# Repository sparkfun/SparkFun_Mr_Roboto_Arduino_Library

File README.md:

Mr. Roboto Kit
========================

[  
*Mr. Roboto Kit (KIT-11257)*](https://www.sparkfun.com/products/11257)

Mr. Roboto is an Arduino-compatible development board designed to be used as a teaching tool for Arduino programming. All of the surface mount components come pre-soldered so a few minutes of simple through-hole soldering is all it takes to get him up and running. After the kit is put together, the on board sensors, buzzer and LCD screen make an excellent platform for learning how to write code for physical computing.

Repository Contents
-------------------

* **/firmware** - Arduino example code
* **/hardware** - PCB design files (created with Eagle 6.1.0)

Product Versions
----------------

**[KIT-11257](https://www.sparkfun.com/products/11257) - Mr. Roboto Kit OEM packaging**  
The Mr. Roboto Kit in standard OEM packaging.

**[RTL-11384](https://www.sparkfun.com/products/11384) - Mr. Roboto Kit retail packaging**  
The Mr. Roboto Kit in a retail-ready plastic clam shell.

License Information
-------------------

All contents of this repository are released under [Creative Commons Share-alike 3.0](http://creativecommons.org/licenses/by-sa/3.0/).

Author
------

Jim Lindblom, [SparkFun Electronics](https://www.sparkfun.com)

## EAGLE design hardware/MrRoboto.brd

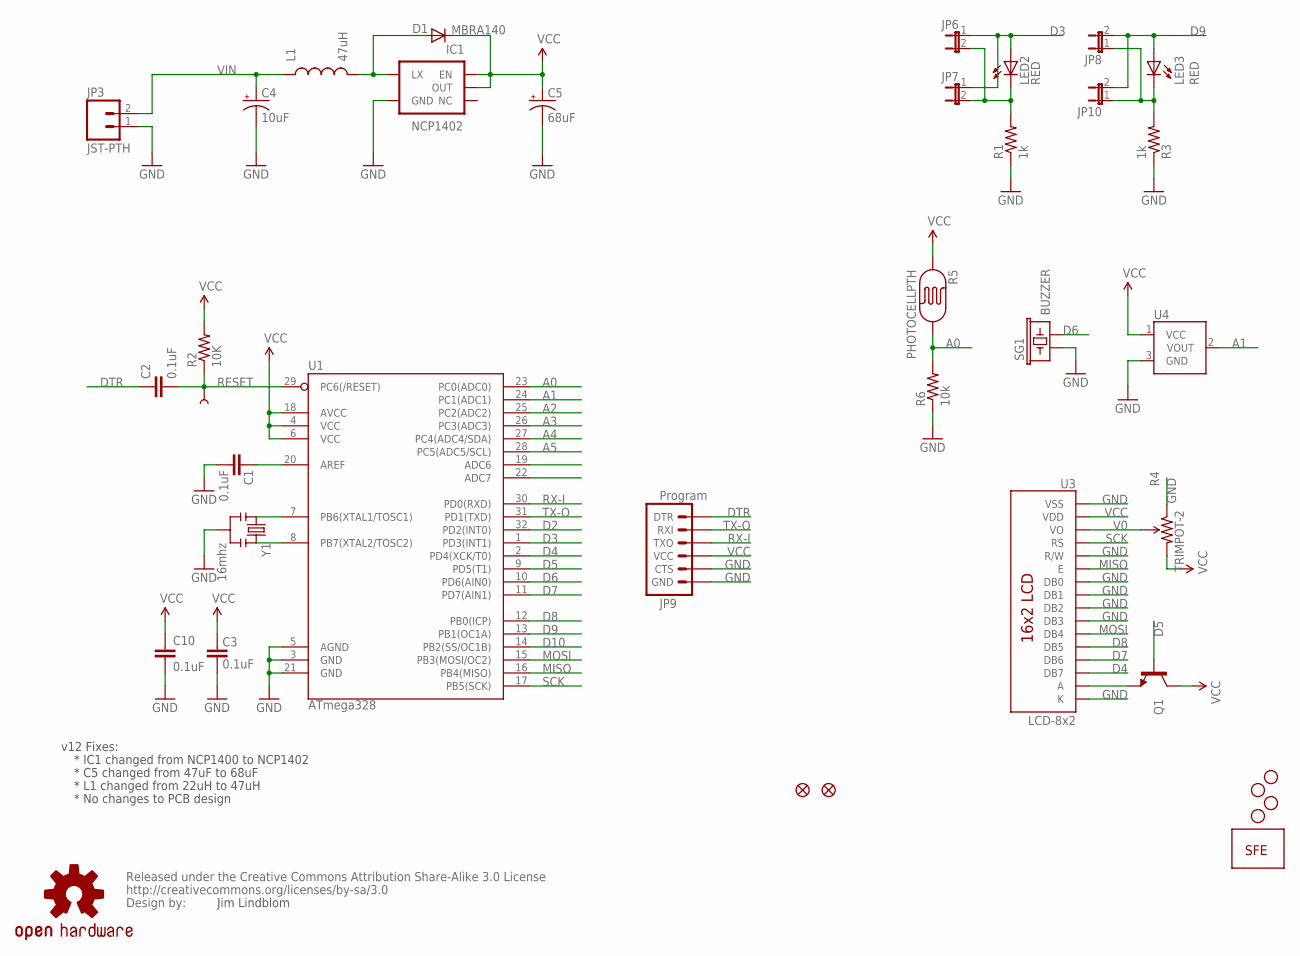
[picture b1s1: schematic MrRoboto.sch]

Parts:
C1, C2, C3, C10: 0.1uF; 0402-CAP
C4: 10uF; EIA3216
C5: 68uF; EIA3528
D1: MBRA140; SMA-DIODE
IC1: NCP1402; SOT23-5
JP1, JP2, JP4, JP5: Long, Plastic; STAND-OFF
JP3: JST-PTH; JST-2-PTH-KIT
JP6, JP7, JP8, JP10: JUMPER-2SMD-NO-NS; SJ_2S-NO-NS
JP9: Program; 1X06-KIT
JP11, JP12: FIDUCIAL1X2.5; FIDUCIAL-1X2.5
L1: 47uH; CR54
LED2, LED3: RED; LED5MM-KIT
Q1: TRANSISTOR_NPNSOT23; SOT23
R1, R3: 1k; AXIAL-0.3-KIT
R2: 10K; 0402-RES
R4: TRIMPOT-2; TRIMPOT_TC33
R5: PHOTOCELLPTH; PHOTOCELL-KIT
R6: 10k; 0402-RES
SG1: BUZZER; BUZZER-12MM-NS-KIT
TP1: TP; PAD.03X.05
U1: ATmega328; TQFP32-08
U3: LCD-8x2; LCD-8X2-KIT
U4: TMP36TO-92-KIT; TO-92-KIT
U$1: CREATIVE_COMMONS
U$2: OSHW-LOGOM; OSHW-LOGO-M
U$3: LOGO-SFENEW; SFE-NEW-WEBLOGO
Y1: 16mhz; RESONATOR-SMD

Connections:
A0: R5.2, R6.2, U1.23 (PC0(ADC0))
A1: U1.24 (PC1(ADC1)), U4.2 (VOUT)
A2: U1.25 (PC2(ADC2))
A3: U1.26 (PC3(ADC3))
A4: U1.27 (PC4(ADC4/SDA))
A5: U1.28 (PC5(ADC5/SCL))
AREF: C1.2, U1.20 (AREF)
D2: U1.32 (PD2(INT0))
D3: JP6.1, JP7.1, LED2.A, U1.1 (PD3(INT1))
D4: U1.2 (PD4(XCK/T0)), U3.14 (DB7)
D5: Q1.1 (B), U1.9 (PD5(T1))
D6: SG1.- (2), U1.10 (PD6(AIN0))
D7: U1.11 (PD7(AIN1)), U3.13 (DB6)
D8: U1.12 (PB0(ICP)), U3.12 (DB5)
D9: JP8.2, JP10.2, LED3.A, U1.13 (PB1(OC1A))
D10: U1.14 (PB2(SS/OC1B))
DTR: C2.1, JP9.1 (DTR)
GND: C1.1, C3.1, C4.C (-), C5.C (-), C10.2, IC1.4 (GND), JP3.1, JP9.5 (CTS), JP9.6 (GND), R1.P$1 (1), R3.P$1 (1), R4.1 (CCW), R6.1, SG1.+ (1), U1.3 (GND), U1.5 (AGND), U1.21 (GND), U3.1 (VSS), U3.5 (R/W), U3.7 (DB0), U3.8 (DB1), U3.9 (DB2), U3.10 (DB3), U3.16 (K), U4.3 (GND), Y1.2
MISO: U1.16 (PB4(MISO)), U3.6 (E)
MOSI: U1.15 (PB3(MOSI/OC2)), U3.11 (DB4)
unnamed: D1.A, IC1.5 (LX), L1.P$2 (2)
unnamed: Q1.2 (E), U3.15 (A)
unnamed: U1.7 (PB6(XTAL1/TOSC1)), Y1.1
unnamed: JP8.1, JP10.1, LED3.K (C), R3.P$2 (2)
unnamed: U1.8 (PB7(XTAL2/TOSC2)), Y1.3
unnamed: JP6.2, JP7.2, LED2.K (C), R1.P$2 (2)
RESET: C2.2, R2.1, TP1.P$1, U1.29 (PC6(/RESET))
RX-I: JP9.3 (TXO), U1.30 (PD0(RXD))
SCK: U1.17 (PB5(SCK)), U3.4 (RS)
TX-O: JP9.2 (RXI), U1.31 (PD1(TXD))
V0: R4.2 (WIPER), U3.3 (VO)
VCC: C3.2, C5.A (+), C10.1, D1.C, IC1.1 (EN), IC1.2 (OUT), JP9.4 (VCC), Q1.3 (C), R2.2, R4.3 (CW), R5.1, U1.4 (VCC), U1.6 (VCC), U1.18 (AVCC), U3.2 (VDD), U4.1 (VCC)
VIN: C4.A (+), JP3.2, L1.P$1 (1)

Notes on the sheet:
Jim Lindblom
v12 Fixes:
* IC1 changed from NCP1400 to NCP1402
* C5 changed from 47uF to 68uF
* L1 changed from 22uH to 47uH
* No changes to PCB design

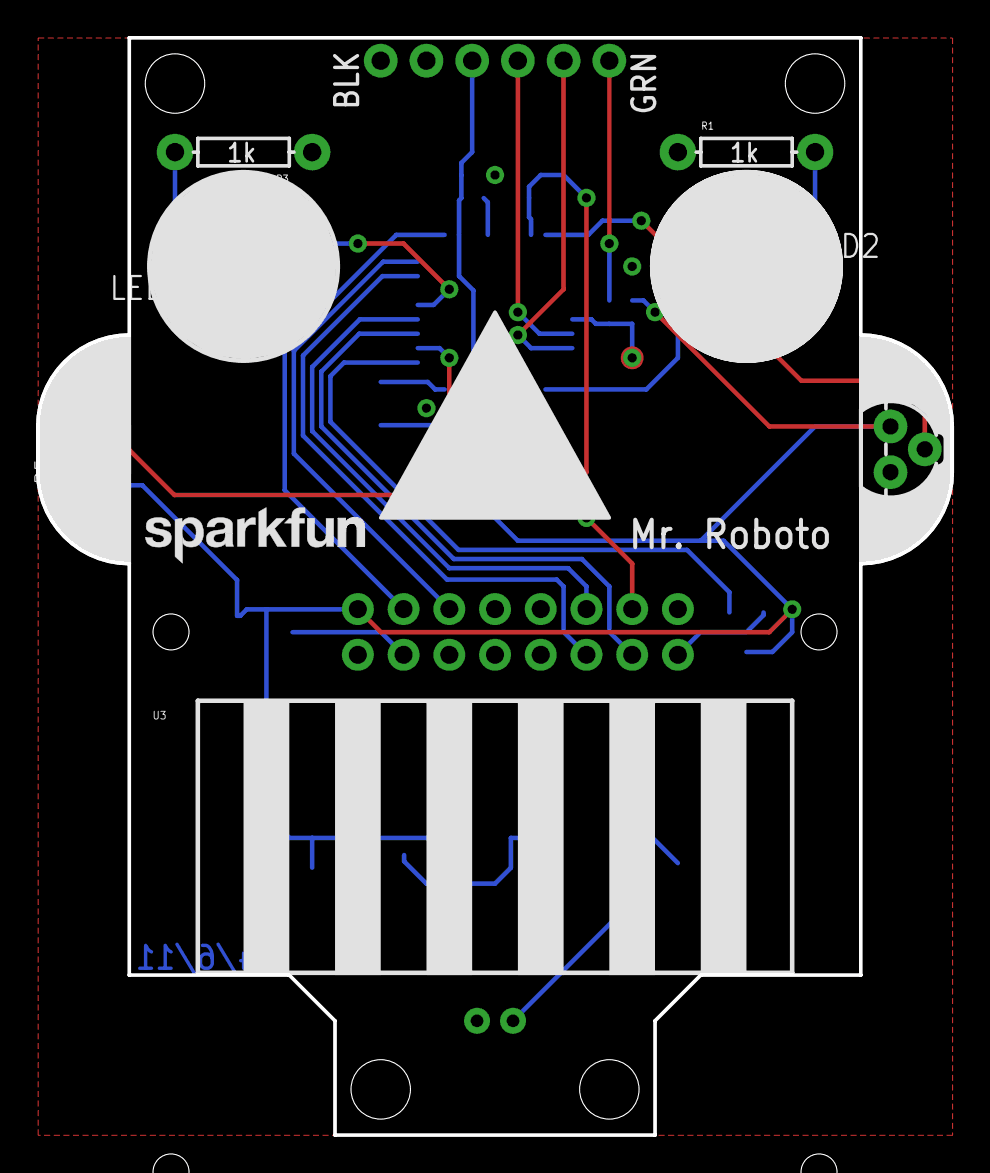
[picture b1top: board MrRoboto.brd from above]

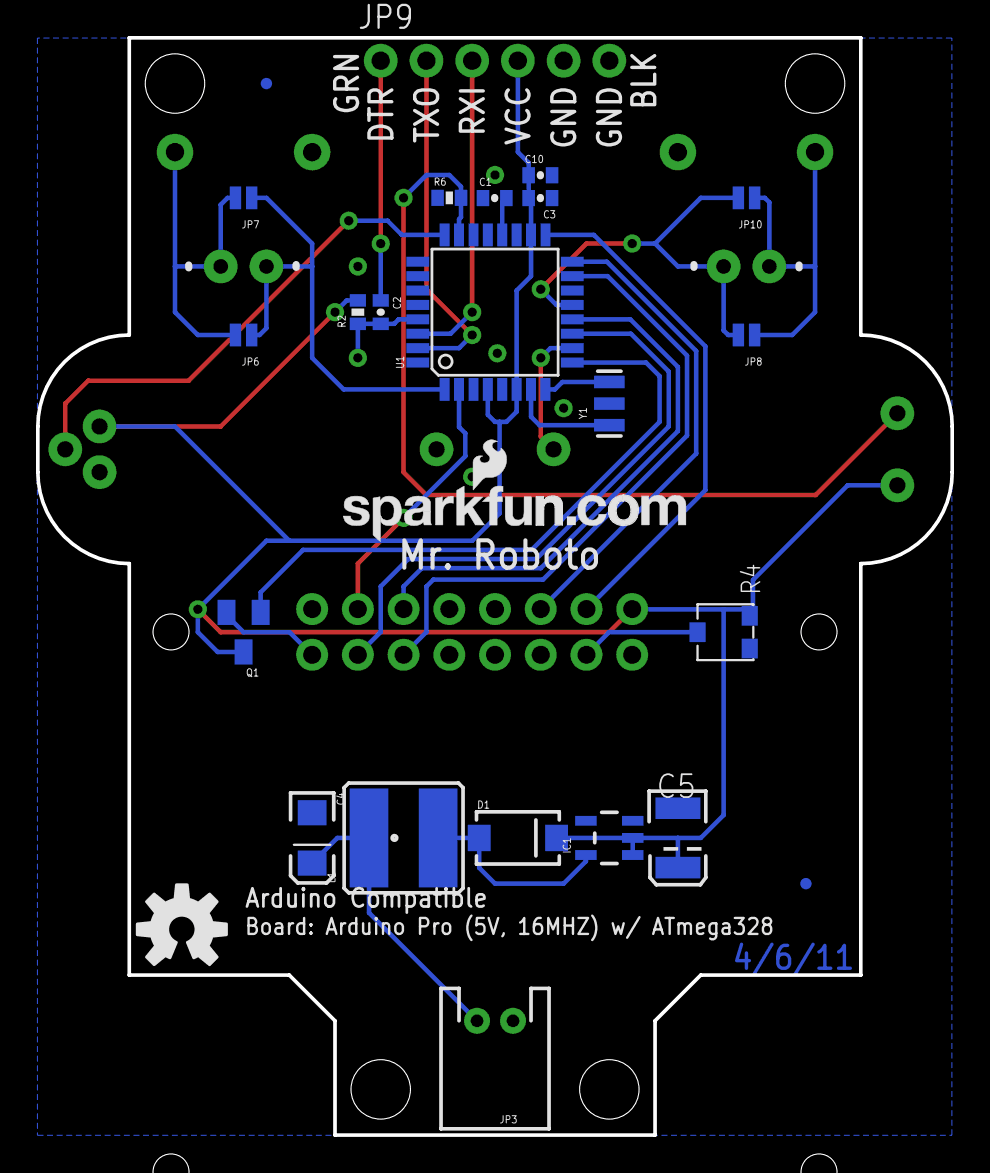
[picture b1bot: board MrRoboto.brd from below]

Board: 2 copper layers, 50.8 x 61.0 mm, 40 parts (25 on the bottom side), 27 nets.

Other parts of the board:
U$11: LOGO-SFENW2; SFE-NEW-WEB

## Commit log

2013-03-20 Initial commit of hardware and readme
2013-03-20 Initial commit of example code
2013-03-20 Markdown-ifying example code readme
2015-04-24 structure update
2015-04-24 Fixing Links
2015-04-24 fixing things
2015-04-24 fixing
2025-06-30 Update README.md
    Updating link

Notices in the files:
parts and their libraries:
SparkFun: Released under the Creative Commons Attribution Share-Alike 3.0 License
